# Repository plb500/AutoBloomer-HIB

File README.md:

# AutoBloomer Hardware Interface Board

Code and PCB design for the Hardware Interface Board, the board used by the Raspberry Pi to process sensor data and trigger relays.

## Features
- Raspberry Pi RTC module
- I2C expander providing up to 8 I2C device slots, along with plug detection pins for the Raspberry Pico
- Sensor multiplexing to Raspberry Pi via Raspberry Pico
- Feed level sensors
- Soil moisture sensing
- SCD30 sensing
- Ports for 8 panel/indicator LEDs
- Raspberry Pi power output ports
- Headers for external Pi shutdown/reset and Pico reset buttons
- Control circuitry and interface for properly driving common 5v relay boards (Sainsmart etc)
- Serial Wire Debug (SWD) pins exposed for debugging/programming Raspberry Pico

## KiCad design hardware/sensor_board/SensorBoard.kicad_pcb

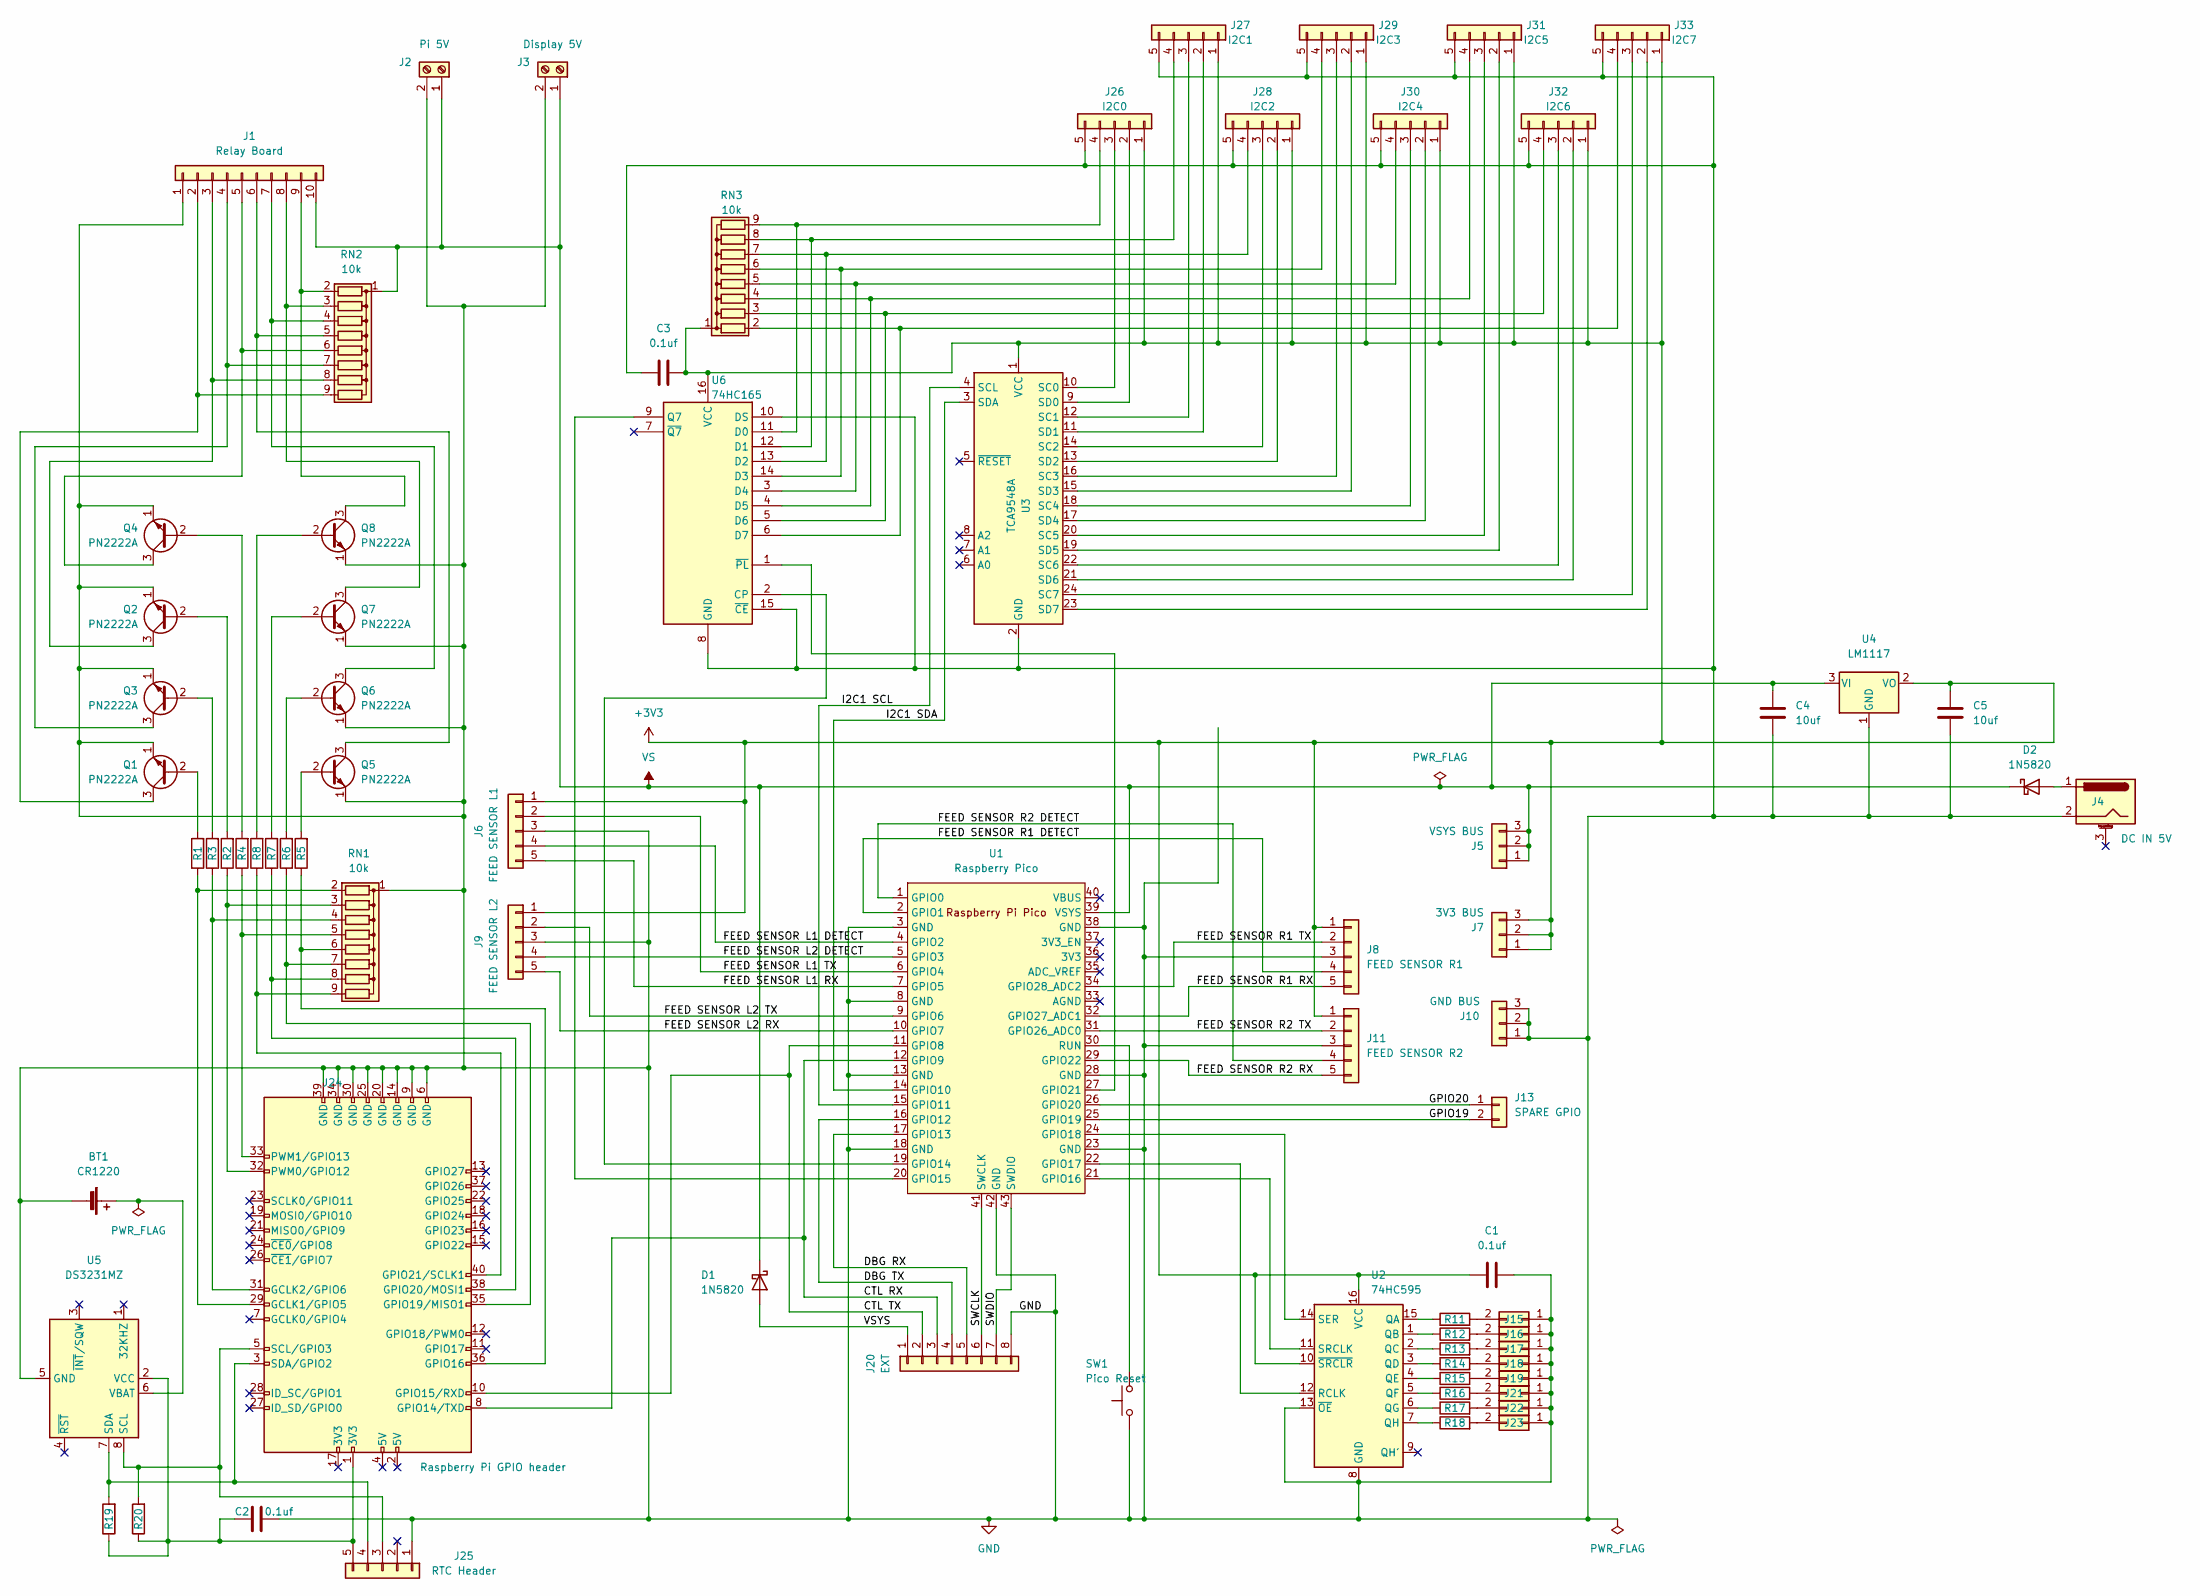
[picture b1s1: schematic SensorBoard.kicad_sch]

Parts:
BT1: CR1220; BatteryHolder_Keystone_3000_1x12mm
C1, C2, C3: 0.1uf; C_Disc_D6.0mm_W2.5mm_P5.00mm
C4, C5: 10uf; C_Disc_D6.0mm_W2.5mm_P5.00mm
D1, D2: 1N5820; D_DO-201AD_P15.24mm_Horizontal
J1: Relay Board; PinHeader_1x10_P2.54mm_Vertical
J2: Pi 5V; JST_XH_B2B-XH-A_1x02_P2.50mm_Vertical
J3: Display 5V; JST_XH_B2B-XH-A_1x02_P2.50mm_Vertical
J4: DC IN 5V; BarrelJack_Horizontal
J5: VSYS BUS; PinHeader_1x03_P2.54mm_Vertical
J6: FEED SENSOR L1; JST_XH_B5B-XH-A_1x05_P2.50mm_Vertical
J7: 3V3 BUS; PinHeader_1x03_P2.54mm_Vertical
J8: FEED SENSOR R1; JST_XH_B5B-XH-A_1x05_P2.50mm_Vertical
J9: FEED SENSOR L2; JST_XH_B5B-XH-A_1x05_P2.50mm_Vertical
J10: GND BUS; PinHeader_1x03_P2.54mm_Vertical
J11: FEED SENSOR R2; JST_XH_B5B-XH-A_1x05_P2.50mm_Vertical
J13: SPARE GPIO; PinHeader_1x02_P2.54mm_Vertical
J15: LED L1; JST_XH_B2B-XH-A_1x02_P2.50mm_Vertical
J16: LED L2; JST_XH_B2B-XH-A_1x02_P2.50mm_Vertical
J17: LED L3; JST_XH_B2B-XH-A_1x02_P2.50mm_Vertical
J18: LED L4; JST_XH_B2B-XH-A_1x02_P2.50mm_Vertical
J19: LED R1; JST_XH_B2B-XH-A_1x02_P2.50mm_Vertical
J20: EXT; JST_XH_B8B-XH-A_1x08_P2.50mm_Vertical
J21: LED R2; JST_XH_B2B-XH-A_1x02_P2.50mm_Vertical
J22: LED R3; JST_XH_B2B-XH-A_1x02_P2.50mm_Vertical
J23: LED R4; JST_XH_B2B-XH-A_1x02_P2.50mm_Vertical
J24: Raspberry Pi GPIO header; PinHeader_2x20_P2.54mm_Vertical
J25: RTC Header; PinHeader_1x05_P2.54mm_Vertical
J26: I2C0; JST_XH_B5B-XH-A_1x05_P2.50mm_Vertical
J27: I2C1; JST_XH_B5B-XH-A_1x05_P2.50mm_Vertical
J28: I2C2; JST_XH_B5B-XH-A_1x05_P2.50mm_Vertical
J29: I2C3; JST_XH_B5B-XH-A_1x05_P2.50mm_Vertical
J30: I2C4; JST_XH_B5B-XH-A_1x05_P2.50mm_Vertical
J31: I2C5; JST_XH_B5B-XH-A_1x05_P2.50mm_Vertical
J32: I2C6; JST_XH_B5B-XH-A_1x05_P2.50mm_Vertical
J33: I2C7; JST_XH_B5B-XH-A_1x05_P2.50mm_Vertical
Q1, Q2, Q3, Q4, Q5, Q6, Q7, Q8: PN2222A; TO-92_Inline
R1, R2, R3, R4, R5, R6, R7, R8: 2.2k; R_Axial_DIN0207_L6.3mm_D2.5mm_P7.62mm_Horizontal
R11, R12, R13: R1; R_Axial_DIN0207_L6.3mm_D2.5mm_P7.62mm_Horizontal
R14: R2; R_Axial_DIN0207_L6.3mm_D2.5mm_P7.62mm_Horizontal
R15: R3; R_Axial_DIN0207_L6.3mm_D2.5mm_P7.62mm_Horizontal
R16: R4; R_Axial_DIN0207_L6.3mm_D2.5mm_P7.62mm_Horizontal
R17: R5; R_Axial_DIN0207_L6.3mm_D2.5mm_P7.62mm_Horizontal
R18: R6; R_Axial_DIN0207_L6.3mm_D2.5mm_P7.62mm_Horizontal
R19, R20: 4.3k; R_Axial_DIN0207_L6.3mm_D2.5mm_P7.62mm_Horizontal
RN1, RN2, RN3: 10k; R_Array_SIP9
SW1: Pico Reset; SW_PUSH_6mm
U1: Raspberry Pico; RPi_Pico_SMD_TH
U2: 74HC595; DIP-16_W7.62mm
U3: TCA9548A; DIP-24_W15.24mm
U4: LM1117; TO-220-3_Horizontal_TabDown
U5: DS3231MZ; SOIC-8_3.9x4.9mm_P1.27mm
U6: 74HC165; DIP-16_W7.62mm

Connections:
+3V3: C1.1, C3.1, C5.1, J6.1, J7.1, J7.2, J7.3, J8.1, J9.1, J11.1, J26.1, J27.1, J28.1, J29.1, J30.1, J31.1, J32.1, J33.1, RN3.1 (common), U2.10 (~SRCLR), U2.16 (VCC), U3.1 (VCC), U4.2 (VO), U6.16 (VCC)
/CTL RX: J20.3, J24.8 (GPIO14/TXD), U1.12 (GPIO9)
/CTL TX: J20.2, J24.10 (GPIO15/RXD), U1.11 (GPIO8)
/DBG RX: J20.5, U1.17 (GPIO13)
/DBG TX: J20.4, U1.16 (GPIO12)
/FEED SENSOR L1 DETECT: J6.4, U1.4 (GPIO2)
/FEED SENSOR L1 RX: J6.5, U1.7 (GPIO5)
/FEED SENSOR L1 TX: J6.2, U1.6 (GPIO4)
/FEED SENSOR L2 DETECT: J9.4, U1.5 (GPIO3)
/FEED SENSOR L2 RX: J9.5, U1.10 (GPIO7)
/FEED SENSOR L2 TX: J9.2, U1.9 (GPIO6)
/FEED SENSOR R1 DETECT: J8.4, U1.2 (GPIO1)
/FEED SENSOR R1 RX: J8.5, U1.32 (GPIO27_ADC1)
/FEED SENSOR R1 TX: J8.2, U1.34 (GPIO28_ADC2)
/FEED SENSOR R2 DETECT: J11.4, U1.1 (GPIO0)
/FEED SENSOR R2 RX: J11.5, U1.29 (GPIO22)
/FEED SENSOR R2 TX: J11.2, U1.31 (GPIO26_ADC0)
/GPIO19: J13.2, U1.25 (GPIO19)
/GPIO20: J13.1, U1.26 (GPIO20)
/I2C1 SCL: U1.15 (GPIO11), U3.4 (SCL)
/I2C1 SDA: U1.14 (GPIO10), U3.3 (SDA)
/SWCLK: J20.6, U1.41 (SWCLK)
/SWDIO: J20.7, U1.43 (SWDIO)
/VSYS: D1.2 (A), J20.1
GND: BT1.2 (-), C1.2, C2.2, C3.2, C4.1, C5.2, J1.1, J2.2, J3.2, J4.2, J6.3, J8.3, J9.3, J10.1, J10.2, J10.3, J11.3, J15.1, J16.1, J17.1, J18.1, J19.1, J20.8, J21.1, J22.1, J23.1, J24.6 (GND), J24.9 (GND), J24.14 (GND), J24.20 (GND), J24.25 (GND), J24.30 (GND), J24.34 (GND), J24.39 (GND), J25.1, J26.5, J27.5, J28.5, J29.5, J30.5, J31.5, J32.5, J33.5, Q1.1 (E), Q2.1 (E), Q3.1 (E), Q4.1 (E), Q5.1 (E), Q6.1 (E), Q7.1 (E), Q8.1 (E), RN1.1 (common), SW1.1, U1.3 (GND), U1.8 (GND), U1.13 (GND), U1.18 (GND), U1.23 (GND), U1.28 (GND), U1.38 (GND), U1.42 (GND), U2.8 (GND), U2.13 (~OE), U3.2 (GND), U4.1 (GND), U5.5 (GND), U6.8 (GND), U6.10 (DS), U6.15 (~CE)
unnamed: BT1.1 (+), U5.6 (VBAT)
unnamed: C2.1, J24.1 (3V3), J25.5, R19.1, R20.1, U5.2 (VCC)
unnamed: D2.2 (A), J4.1
unnamed: J1.2, Q1.3 (C), RN2.9 (R8)
unnamed: J1.3, Q2.3 (C), RN2.8 (R7)
unnamed: J1.4, Q3.3 (C), RN2.7 (R6)
unnamed: J1.5, Q4.3 (C), RN2.6 (R5)
unnamed: J1.6, Q5.3 (C), RN2.5 (R4)
unnamed: J1.7, Q6.3 (C), RN2.4 (R3)
unnamed: J1.8, Q7.3 (C), RN2.3 (R2)
unnamed: J1.9, Q8.3 (C), RN2.2 (R1)
unnamed: J15.2, R11.2
unnamed: J16.2, R12.2
unnamed: J17.2, R13.2
unnamed: J18.2, R14.2
unnamed: J19.2, R15.2
unnamed: J21.2, R16.2
unnamed: J22.2, R17.2
unnamed: J23.2, R18.2
unnamed: J24.3 (SDA/GPIO2), J25.4, R19.2, U5.7 (SDA)
unnamed: J24.5 (SCL/GPIO3), J25.3, R20.2, U5.8 (SCL)
unnamed: J24.29 (GCLK1/GPIO5), R1.1, RN1.2 (R1)
unnamed: J24.31 (GCLK2/GPIO6), R3.1, RN1.4 (R3)
unnamed: J24.32 (PWM0/GPIO12), R2.1, RN1.3 (R2)
unnamed: J24.33 (PWM1/GPIO13), R4.1, RN1.5 (R4)
unnamed: J24.35 (GPIO19/MISO1), R6.1, RN1.7 (R6)
unnamed: J24.36 (GPIO16), R5.1, RN1.6 (R5)
unnamed: J24.38 (GPIO20/MOSI1), R7.1, RN1.8 (R7)
unnamed: J24.40 (GPIO21/SCLK1), R8.1, RN1.9 (R8)
unnamed: J26.2, U3.9 (SD0)
unnamed: J26.3, U3.10 (SC0)
unnamed: J26.4, RN3.9 (R8), U6.11 (D0)
unnamed: J27.2, U3.11 (SD1)
unnamed: J27.3, U3.12 (SC1)
unnamed: J27.4, RN3.8 (R7), U6.12 (D1)
unnamed: J28.2, U3.13 (SD2)
unnamed: J28.3, U3.14 (SC2)
unnamed: J28.4, RN3.7 (R6), U6.13 (D2)
unnamed: J29.2, U3.15 (SD3)
unnamed: J29.3, U3.16 (SC3)
unnamed: J29.4, RN3.6 (R5), U6.14 (D3)
unnamed: J30.2, U3.17 (SD4)
unnamed: J30.3, U3.18 (SC4)
unnamed: J30.4, RN3.5 (R4), U6.3 (D4)
unnamed: J31.2, U3.19 (SD5)
unnamed: J31.3, U3.20 (SC5)
unnamed: J31.4, RN3.4 (R3), U6.4 (D5)
unnamed: J32.2, U3.21 (SD6)
unnamed: J32.3, U3.22 (SC6)
unnamed: J32.4, RN3.3 (R2), U6.5 (D6)
unnamed: J33.2, U3.23 (SD7)
unnamed: J33.3, U3.24 (SC7)
unnamed: J33.4, RN3.2 (R1), U6.6 (D7)
unnamed: Q1.2 (B), R1.2
unnamed: Q2.2 (B), R2.2
unnamed: Q3.2 (B), R3.2
unnamed: Q4.2 (B), R4.2
unnamed: Q5.2 (B), R5.2
unnamed: Q6.2 (B), R6.2
unnamed: Q7.2 (B), R7.2
unnamed: Q8.2 (B), R8.2
unnamed: R11.1, U2.15 (QA)
unnamed: R12.1, U2.1 (QB)
unnamed: R13.1, U2.2 (QC)
unnamed: R14.1, U2.3 (QD)
unnamed: R15.1, U2.4 (QE)
unnamed: R16.1, U2.5 (QF)
unnamed: R17.1, U2.6 (QG)
unnamed: R18.1, U2.7 (QH)
unnamed: SW1.2, U1.30 (RUN)
unnamed: U1.19 (GPIO14), U6.2 (CP)
unnamed: U1.20 (GPIO15), U6.9 (Q7)
unnamed: U1.21 (GPIO16), U2.11 (SRCLK)
unnamed: U1.22 (GPIO17), U2.12 (RCLK)
unnamed: U1.24 (GPIO18), U2.14 (SER)
unnamed: U1.27 (GPIO21), U6.1 (~PL)
VS: C4.2, D1.1 (K), D2.1 (K), J1.10, J2.1, J3.1, J5.1, J5.2, J5.3, RN2.1 (common), U1.39 (VSYS), U4.3 (VI)

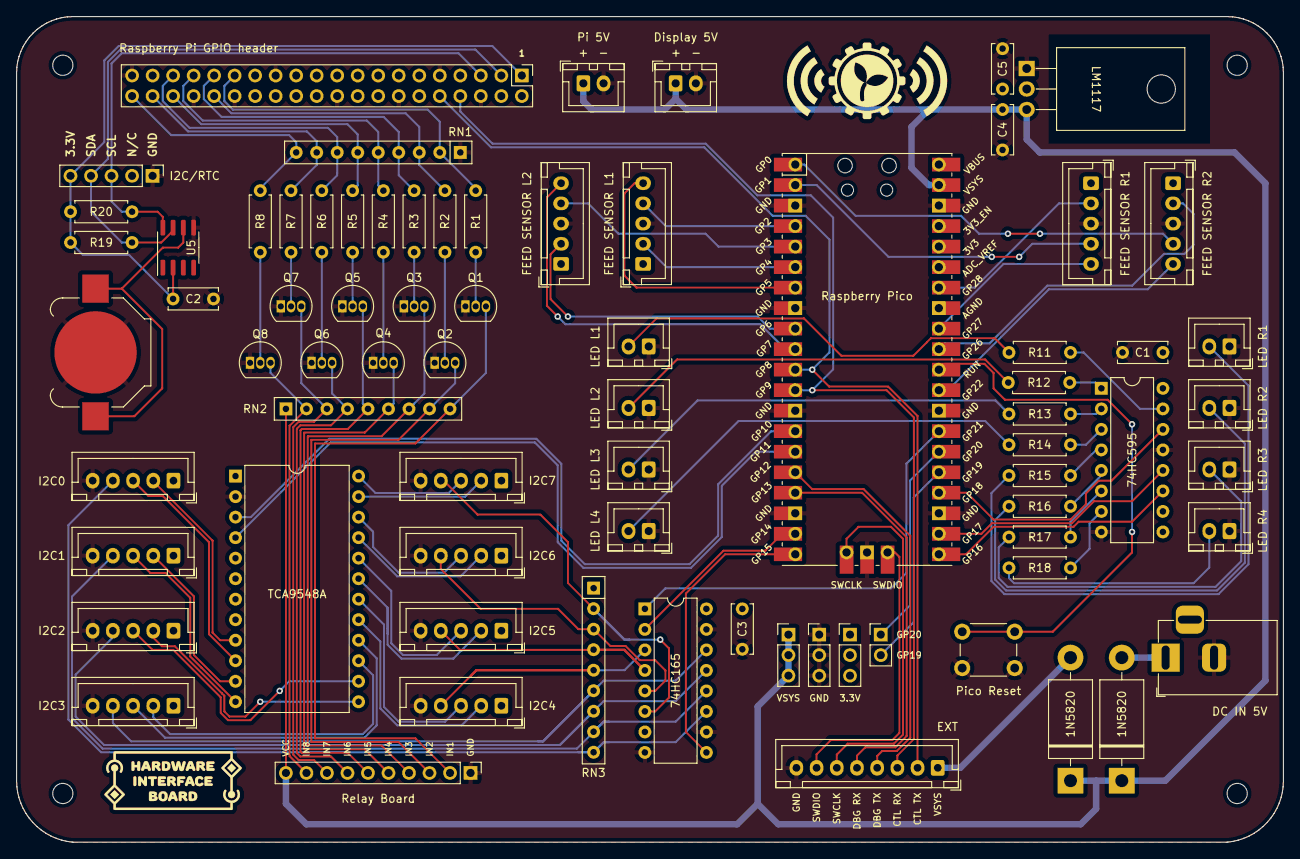
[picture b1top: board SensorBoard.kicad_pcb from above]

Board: 2 copper layers, 156.9 x 102.2 mm, 79 parts (0 on the bottom side), 102 nets.

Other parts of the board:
H1, H2, H3, H4: MountingHole_2.5mm

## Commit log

2022-02-05 Initial repo dump
2022-07-15 Made a sensor simulator just to make it a bit easier to write the serial processing on the main controller
2022-07-17 Think I have a pretty workable interface for sending back generic sensor details/data. Tested inside of a python sample app in Controller repo
2022-07-17 Adding a startup signal to the simulator. Probably won't be necessary on the real device but it's required on the Arduino serial
2022-07-24 Overhauling serial responses. No longer splitting up descriptions from data. There is no point to doing this currently
2022-08-05 Rewrote Pico controller to completely use msgpack for serial comms and fixed as many bugs as I could find. Basic functionality looks to be working. Haven't test with full suite of sensors yet.
2022-08-05 Some code housekeeping
2022-08-05 Swap L and R hardware definitions to match box orientation. Some more code housekeeping
2022-08-05 Fixed some naming and added a send ready command and response
2022-08-07 Making load sensor calibratable. Plus making it a bit easier to calibrate other sensors should we need to
2022-08-18 PCB for sensor controller, some other sensor controller hardware files (CNC stuff etc)
2022-09-13 Massive sensor controller update. Removed weight sensor for feed levels, replaced with sonar. Lots of other code improvements, including read/update loop speed adn configuration changes to match PCB 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
2022-09-13 PCB v2.0. Using sonars instead of load cells, which frees up the tare buttons. Also using a shift register for LEDs instead of direct GPIO control which frees up three more pins.
2022-09-13 Some CNC files for load cell mounts (defunct) and sonar sensor frames (funct)
2022-09-13 Don't need to keep that there
2022-09-13 Getting all OCD about a diagram that nobody except me will ever see
2022-09-13 Some more doc/graphics stuff
2022-09-13 Fixed error in shift register wiring
2022-09-13 Forgot to actually copy across sonar values into msgpack
2022-09-13 Setting export directory
2022-10-26 Fixing up hardware definitions to match new board layout. Fixing some minor issues with hotplugging
2022-12-12 Updating some schematics
2022-12-12 Matching pins in code up to actual board layout
2022-12-12 Tidying up PCB a little bit
2022-12-12 Pushing up some old sim codem which may or may not work any more
2023-01-31 Doc/graphics updates
2023-01-31 Brand new sensor board, includes I2C expander, RTC and relay board connections
2023-02-02 New version without DHT22. Full exposed I2C expander
2023-02-03 Completely revamped board. Will fully use the I2C expander now to have one "sensor pod" per grow system containing an SCD30 and a soil sensor. This allows for 8 sensor pods. Will reuse the I2C interf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
2023-02-03 Beautifying board
2023-02-04 More OCD tweaking
2023-02-04 Final 3.0 tweakage. Gerbers sent to OSHPark
2023-02-09 Attempting to switch back to a multicore implementation. Changing data structure to better support transferring live sensor data between cores
2023-02-09 Refactoring msgpack wrappers to support multicore
2023-02-10 Refactoring completed. Need to test on actual hardware now
2023-02-17 Some final tidy up and housekeeping plus fixing bug which was causing delayed startup (we weren't sending the controller ready packet properly(
2023-03-18 Butchering my way through the code, integrating the new sensor pod.
2023-03-18 Think everything is wrangled together now. Tests show comms to sensors working. Multicore serial comms looks to be a lot faster. Still some inefficiencies in how we are storing the sensor data.
2023-03-18 Files for sensor pod enclosure and hardware interface board/controller housing
2023-03-18 Moved everything out of the sensor pod interface file and into individual headers again. It was too clunky and weird. Didn't like it. Tidied up some things and fixed a timing bug for the sift registe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
2023-10-14 Adjusting constants to match board setup
2023-10-14 Merge multicore into main branch (#1)
    * Attempting to switch back to a multicore implementation. Changing data structure to better support transferring live sensor data between cores
    * Refactoring msgpack wrappers to support multicore
    * Refactoring completed. Need to test on actual hardware now
    * Some final tidy up and housekeeping plus fixing bug which was causing delayed startup (we weren't sending the controller ready packet properly(
    * Butchering my way through the code, integrating the new sensor pod.
    * Think everything is wrangled together now. Tests show comms to sensors working. Multicore serial comms looks to be a lot faster. Still some inefficiencies in how we are st
2023-10-14 Modifying HIB to include relay pull jumper (for defaulting relay inputs to HIGH or LOW on startup)
2023-10-15 Whole bunch of CNC files for various updates/new parts
2023-10-15 Trying out the idea of a hardware hat for the Pi rather than a whole separate board. Doesn't fit in my enclosure, though
2023-10-19 Board revisions 3.1 - added mutiple external switch connectors, clock battery sensing path to pico, jumpers to control feed sensor outputs and relay pulls
2023-10-21 Repo cleanup/housekeeping
2023-10-21 Starting to add stuff for README
2023-11-09 Adding rudimentary bettery sensor. Matching hardware pin definitions to new board revision
2023-12-14 First crack at fixing the sensor pod stalling. Adding extra logging and some depth to I2C functions
2023-12-14 Adding in sensor pod watchdog. Will attempt to reset hardware if it doesn't respond
2023-12-16 Can reset watchdog timer if we only have one reading
2023-12-26 Fixing up a bug with not resetting sensor pod properly. Adjusting hardware definitions to match actual hardware
2023-12-26 Trying to free up Pico pins by using another shift register
2024-01-01 Board arrangement/tidying
2024-01-02 (Hopefully) adding in the ability to reset the multiplexer if it gets stuck adn starts timing out
2024-01-03 New board revision - main change is a better RTC battery sensing circuit. Also general board tidying/improvements, cleaned up the graphics folder, updated some graphics etc
2024-01-04 Added in some badly set resistor values
2024-01-10 Allowing I2C bus to be reset independently from I2C sensors and supporting chained shift registers
2024-01-10 Tidying up some labeling on PCB
2024-01-12 Part 1 - switching all hardware connect detect to the shift register hardware solution
2024-01-12 Adding new, better battery sensing code (MOSFET-based circuit)
2024-01-12 Tidying up constant definitions
2024-01-12 First blast with MQTT. More or less working. Have wifi connecting, MQTT connecting and publishing
2024-01-12 Adding files read by CMake to set connection/security options
2024-01-12 So I don't accidentally upload wifi key
2024-01-12 Trying to get gitignore to work
2024-01-12 Maybe this?
2024-01-12 gitignore is not the right way to do this
2024-01-12 Some general housekeeping. Making JSON values actual types rather than strings
2024-01-15 Improving the network code, trying to make it more resilient to disconnects etc

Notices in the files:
hardware/sensor_board/SensorBoard.kicad_pcb:
© AutoBloomer.com 2023
